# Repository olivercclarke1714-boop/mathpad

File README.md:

# MathPad – 4x4 Custom Mechanical Keypad

## Description

MathPad is a compact 4x4 mechanical keypad designed for fast numeric and math input.  
Its primary purpose is to provide a customizable keypad for productivity, coding, or creative projects.  
The keyboard features a Seeed XIAO RP2040 microcontroller, fully programmable firmware via KMK, and a small OLED display for dynamic feedback or animations.  

---

### Build Tips

- Test the board before assembling the case  
- Be cautious with LED soldering

---

## Bill of Materials (BOM)

| Qty | Part | Description |
|-----|------|-------------|
| 1   | Seeed XIAO RP2040 | MCU with USB-C and GPIO pins |
| 16  | MX Mechanical Switches | 4x4 grid layout |
| 16  | Keycaps | Compatible with MX switches |
| 16  | 1N4148 Diodes | THT, one per switch for matrix isolation |
| 16  | SK6812 MINI-E LEDs | Addressable RGB LEDs for backlighting |
| 1   | 0.91" OLED Display | I2C 128x32 display for status/animations |
| 2   | 3D Printed Parts | Top and bottom case halves |
| 4   | M3x16mm Screws | Case assembly |
| 4   | Heatset Inserts | For threaded screw holes in the case |
| 1   | PCB | 4x4 keypad matrix with diodes and LED traces |

---

## Firmware

Firmware is written using **KMK (Keyboard Microcontroller Kit)** for Python.  
- Supports 16 key matrix
- Controls 16 SK6812 LEDs for animations  
- Updates the OLED display with custom text or image frames  

The firmware is stored in the `firmware/` folder and can be flashed directly to the Seeed XIAO RP2040.  

OLED Animations
- The 0.91" OLED displays 128×32 1-bit BMP frames from `firmware/animations/`.  
- 1. Put BMPs (128×32) in `animations/`.  
- 2. Name sequentially (e.g., `frame_01.bmp`, `frame_02.bmp`).  
- 3. Flash firmware to the XIAO RP2040.  
- The firmware cycles through frames automatically.

---

## CAD / Case

The case was designed in **Fusion 360** for 3D printing.  

- Top and bottom halves include heatset inserts for M3 screws and mounting points for the PCB.  

---

## PCB & Schematic

PCB designed in **KiCad**.  

- 4x4 switch matrix with THT 1N4148 diodes for each switch  
- Integrated 16x SK6812 LEDs for backlighting  
- 0.91" I2C OLED display included   

---

## Conclusion

MathPad demonstrates a complete, custom 4x4 mechanical keypad project:  
- Hardware: PCB, mechanical switches, LEDs, and OLED  
- Firmware: Fully programmable Python KMK firmware  
- Case: 3D printed top and bottom halves  

It can be used for math input, shortcuts, creative coding, or as a base for custom keypad projects.  

All production-ready files, including **gerbers.zip** and STL case files, are included in the `Production/` folder for easy replication.

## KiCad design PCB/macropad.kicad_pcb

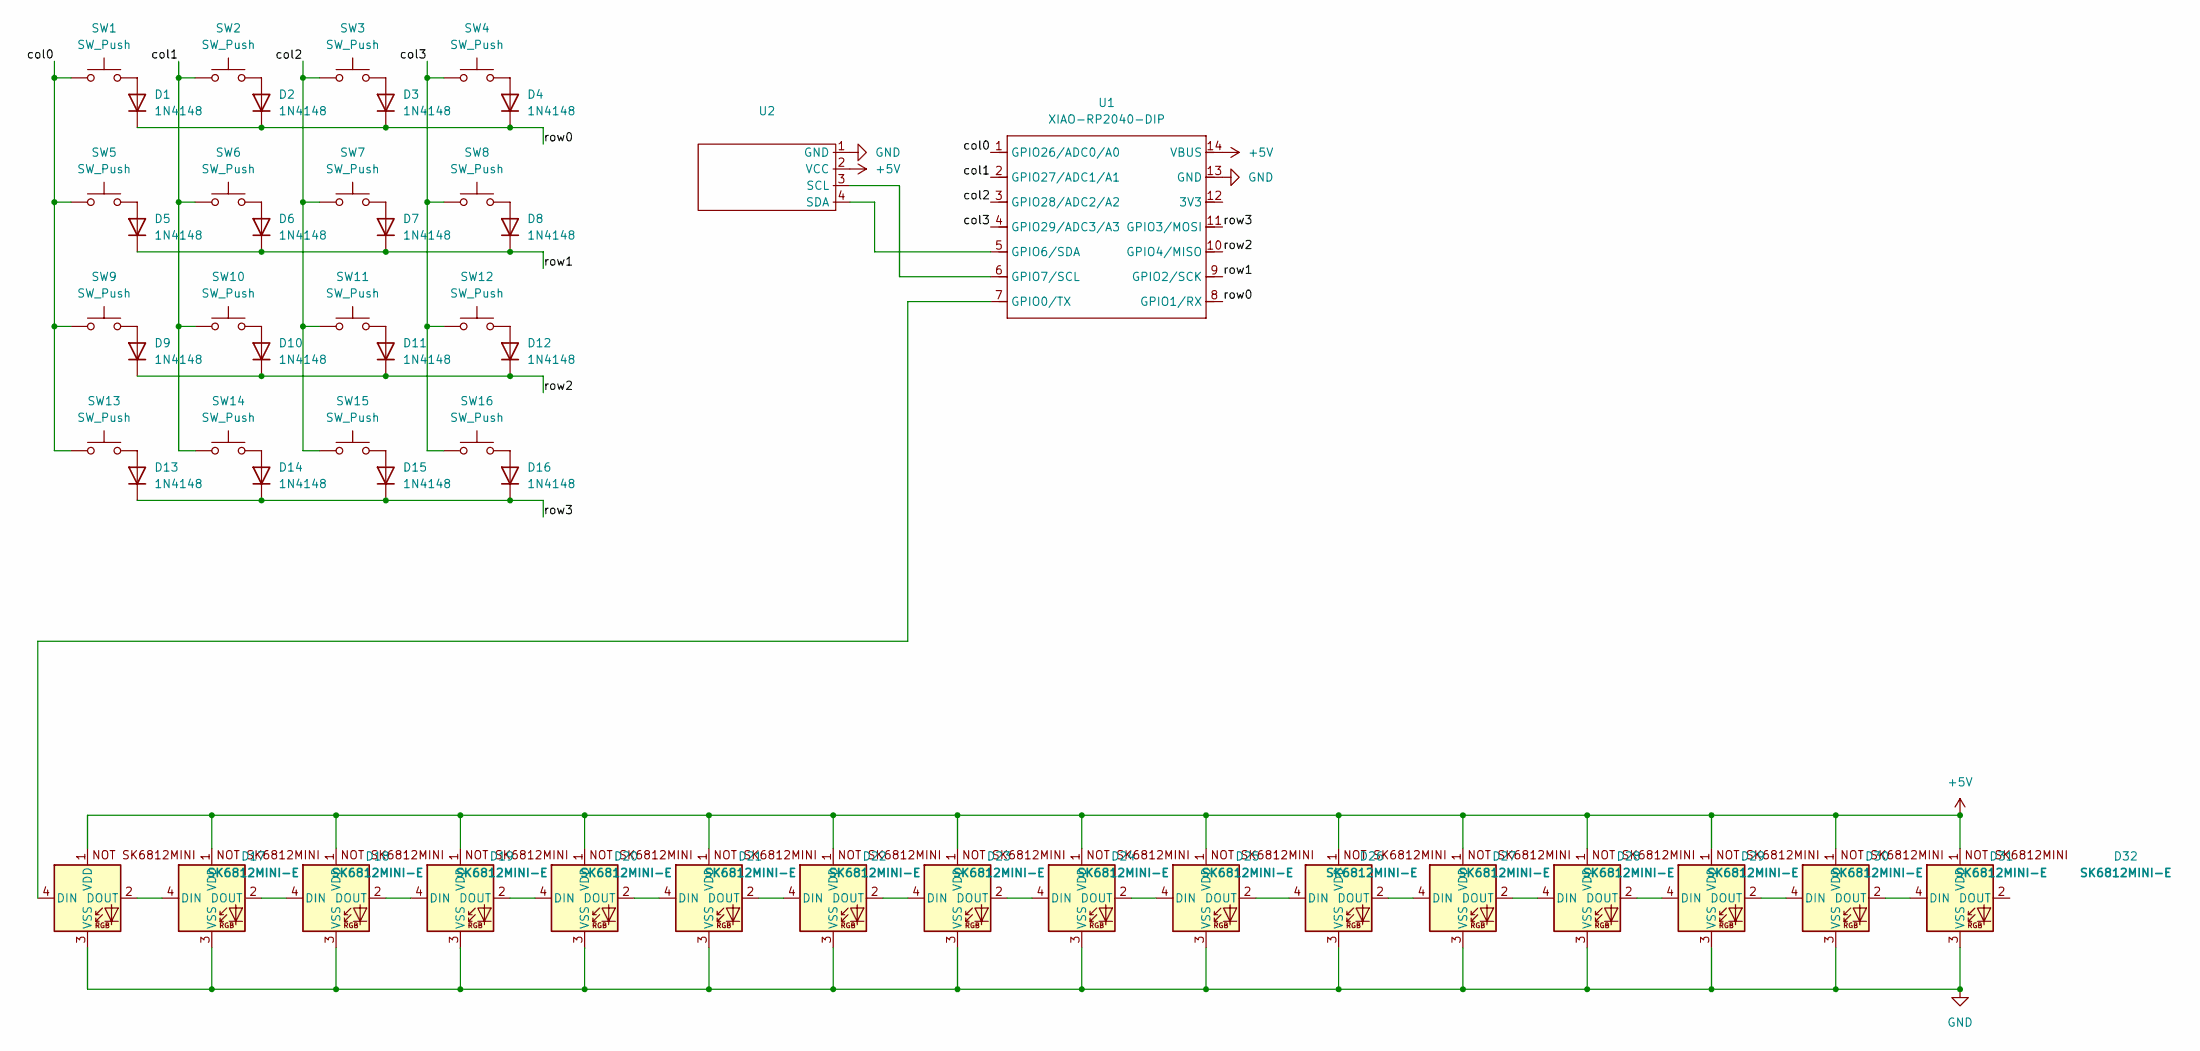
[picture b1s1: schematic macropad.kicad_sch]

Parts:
D1, D2, D3, D4, D5, D6, D7, D8, D9, D10, D11, D12, D13, D14, D15, D16: 1N4148; D_DO-35_SOD27_P7.62mm_Horizontal
D17, D18, D19, D20, D21, D22, D23, D24, D25, D26, D27, D28, D29, D30, D31, D32: SK6812MINI-E; MX_SK6812MINI-E_REV
SW1, SW2, SW3, SW4, SW5, SW6, SW7, SW8, SW9, SW10, SW11, SW12, SW13, SW14, SW15, SW16: SW_Push; SW_Cherry_MX_1.00u_PCB
U1: XIAO-RP2040-DIP
U2: SSD1306-0.91-OLED-4pin-128x32

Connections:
/col0: SW1.1, SW5.1, SW9.1, SW13.1, U1.1 (GPIO26/ADC0/A0)
/col1: SW2.1, SW6.1, SW10.1, SW14.1, U1.2 (GPIO27/ADC1/A1)
/col2: SW3.1, SW7.1, SW11.1, SW15.1, U1.3 (GPIO28/ADC2/A2)
/col3: SW4.1, SW8.1, SW12.1, SW16.1, U1.4 (GPIO29/ADC3/A3)
/row0: D1.1 (K), D2.1 (K), D3.1 (K), D4.1 (K), U1.8 (GPIO1/RX)
/row1: D5.1 (K), D6.1 (K), D7.1 (K), D8.1 (K), U1.9 (GPIO2/SCK)
/row2: D9.1 (K), D10.1 (K), D11.1 (K), D12.1 (K), U1.10 (GPIO4/MISO)
/row3: D13.1 (K), D14.1 (K), D15.1 (K), D16.1 (K), U1.11 (GPIO3/MOSI)
unnamed: D1.2 (A), SW1.2
unnamed: D2.2 (A), SW2.2
unnamed: D3.2 (A), SW3.2
unnamed: D4.2 (A), SW4.2
unnamed: D5.2 (A), SW5.2
unnamed: D6.2 (A), SW6.2
unnamed: D7.2 (A), SW7.2
unnamed: D8.2 (A), SW8.2
unnamed: D9.2 (A), SW9.2
unnamed: D10.2 (A), SW10.2
unnamed: D11.2 (A), SW11.2
unnamed: D12.2 (A), SW12.2
unnamed: D13.2 (A), SW13.2
unnamed: D14.2 (A), SW14.2
unnamed: D15.2 (A), SW15.2
unnamed: D16.2 (A), SW16.2
unnamed: D17.4 (DIN), U1.7 (GPIO0/TX)
unnamed: D17.2 (DOUT), D18.4 (DIN)
unnamed: D18.2 (DOUT), D19.4 (DIN)
unnamed: D19.2 (DOUT), D20.4 (DIN)
unnamed: D20.2 (DOUT), D21.4 (DIN)
unnamed: D21.2 (DOUT), D22.4 (DIN)
unnamed: D22.2 (DOUT), D23.4 (DIN)
unnamed: D23.2 (DOUT), D24.4 (DIN)
unnamed: D24.2 (DOUT), D25.4 (DIN)
unnamed: D25.2 (DOUT), D26.4 (DIN)
unnamed: D26.2 (DOUT), D27.4 (DIN)
unnamed: D27.2 (DOUT), D28.4 (DIN)
unnamed: D28.2 (DOUT), D29.4 (DIN)
unnamed: D29.2 (DOUT), D30.4 (DIN)
unnamed: D30.2 (DOUT), D31.4 (DIN)
unnamed: D31.2 (DOUT), D32.4 (DIN)
unnamed: U1.5 (GPIO6/SDA), U2.4 (SDA)
unnamed: U1.6 (GPIO7/SCL), U2.3 (SCL)

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
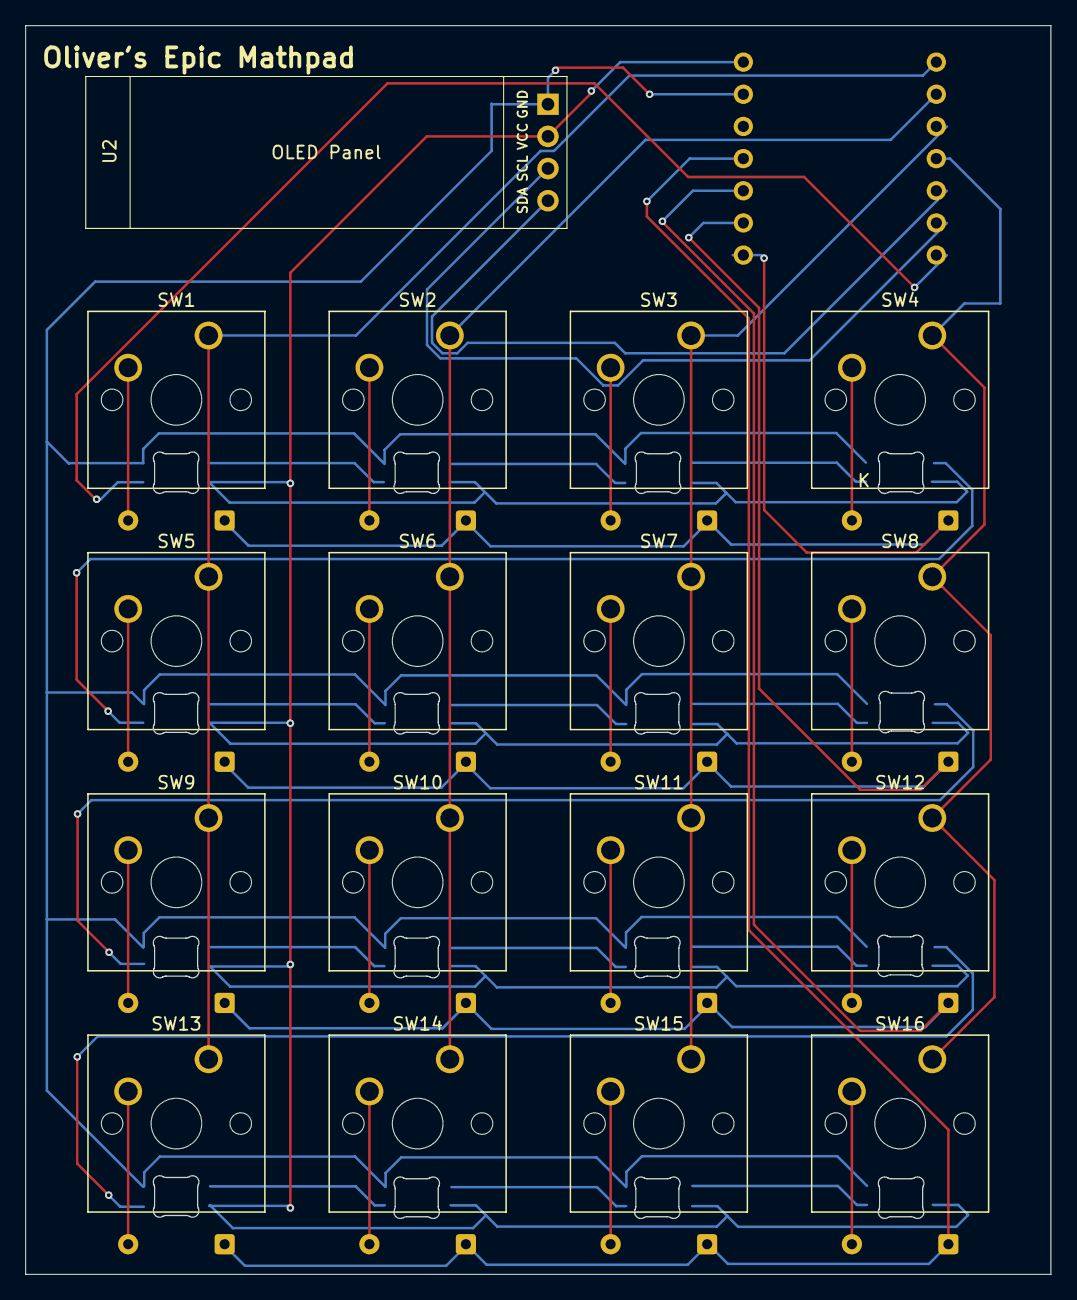
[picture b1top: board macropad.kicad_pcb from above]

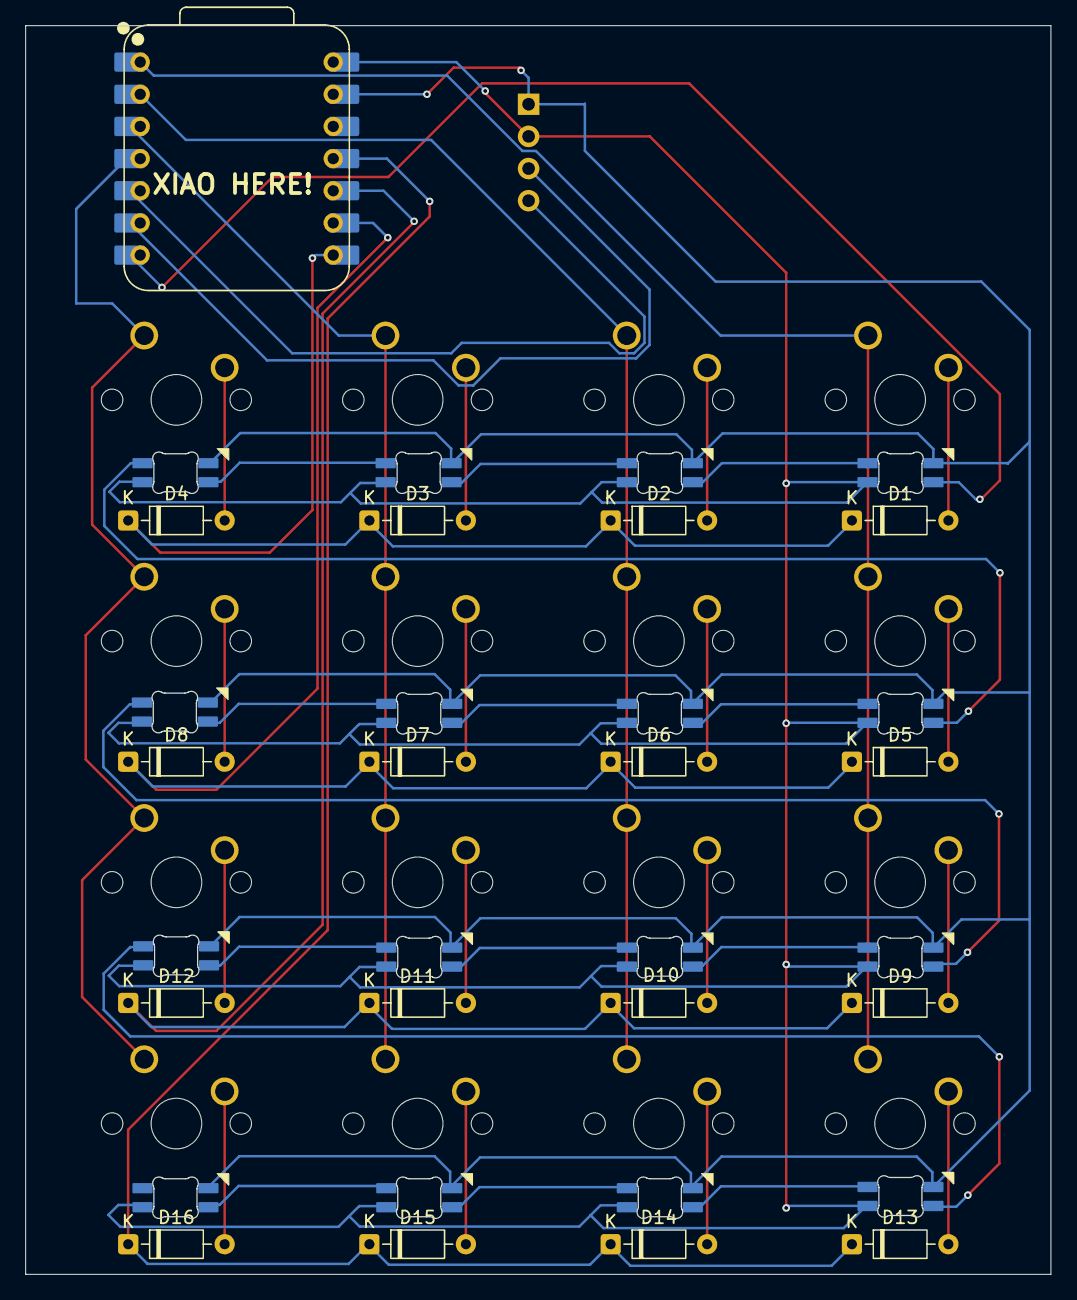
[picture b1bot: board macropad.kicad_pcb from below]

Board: 2 copper layers, 81.0 x 98.6 mm, 50 parts (17 on the bottom side), 44 nets.

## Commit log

2026-02-02 Update README with project specifications
    Added detailed specifications and components list for the Mathpad project.
2026-02-21 omit
2026-02-21 readme
    Updated README.md to enhance project description and details.
2026-02-21 README
2026-02-21 Update README.md
    Removed note about diode requirement for OLED display.
2026-04-03 Add build tips to README
    Added build tips section with testing and soldering advice.
2026-04-03 Fix image filename case in README
2026-04-03 Update build image in README
